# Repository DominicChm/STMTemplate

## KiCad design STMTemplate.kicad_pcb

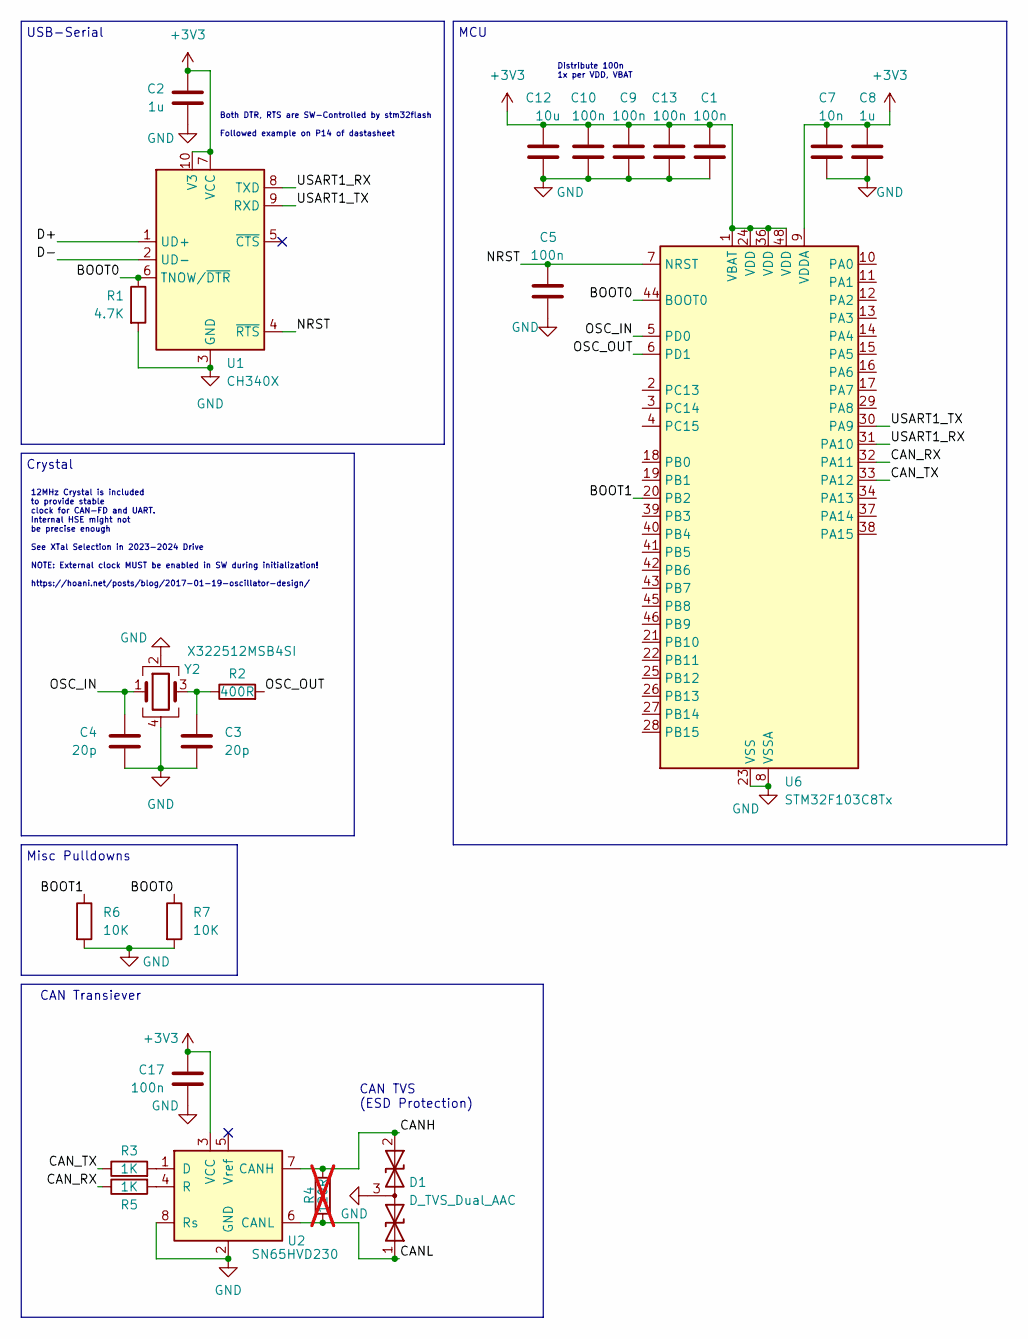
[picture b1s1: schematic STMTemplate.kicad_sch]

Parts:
C1, C5, C9, C10, C13, C17: 100n; C_0402_1005Metric
C2, C8: 1u; C_0402_1005Metric
C3, C4: 20p; C_0402_1005Metric
C7: 10n; C_0402_1005Metric
C12: 10u; C_0402_1005Metric
D1: D_TVS_Dual_AAC; SOT-23-3; LCSC C32677
R1: 4.7K; R_0402_1005Metric
R2: 400R; R_0402_1005Metric
R3, R5: 1K; R_0402_1005Metric
R4: 120R; R_1206_3216Metric; not fitted
R6, R7: 10K; R_0402_1005Metric
U1: CH340X; MSOP-10_3x3mm_P0.5mm
U2: SN65HVD230; SOIC-8_3.9x4.9mm_P1.27mm
U6: STM32F103C8Tx; LQFP-48_7x7mm_P0.5mm
Y2: X322512MSB4SI; Crystal_SMD_3225-4Pin_3.2x2.5mm; LCSC C9002

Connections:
+3V3: C1.1, C2.1, C7.1, C8.1, C9.1, C10.1, C12.1, C13.1, C17.1, U1.7 (VCC), U1.10 (V3), U2.3 (VCC), U6.1 (VBAT), U6.9 (VDDA), U6.24 (VDD), U6.36 (VDD), U6.48 (VDD)
/BOOT0: R1.1, R7.1, U1.6 (TNOW/~DTR), U6.44 (BOOT0)
/BOOT1: R6.1, U6.20 (PB2)
/CANH: D1.2 (A2), R4.1, U2.7 (CANH)
/CANL: D1.1 (A1), R4.2, U2.6 (CANL)
/CAN_RX: R5.1, U6.32 (PA11)
/CAN_TX: R3.1, U6.33 (PA12)
/D+: U1.1 (UD+)
/D-: U1.2 (UD-)
/NRST: C5.1, U1.4 (~RTS), U6.7 (NRST)
/OSC_IN: C4.1, U6.5 (PD0), Y2.1
/OSC_OUT: R2.2, U6.6 (PD1)
/USART1_RX: U1.8 (TXD), U6.31 (PA10)
/USART1_TX: U1.9 (RXD), U6.30 (PA9)
GND: C1.2, C2.2, C3.2, C4.2, C5.2, C7.2, C8.2, C9.2, C10.2, C12.2, C13.2, C17.2, D1.3 (common), R1.2, R6.2, R7.2, U1.3 (GND), U2.2 (GND), U2.8 (Rs), U6.8 (VSSA), U6.23 (VSS), U6.35 (VSS), U6.47 (VSS), Y2.2, Y2.4
unnamed: C3.1, R2.1, Y2.3
unnamed: R3.2, U2.1 (D)
unnamed: R5.2, U2.4 (R)

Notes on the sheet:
USB-Serial
Crystal
Misc Pulldowns
Distribute 100n 1x per VDD, VBAT
https://hoani.net/posts/blog/2017-01-19-oscillator-design/
CAN TVS (ESD Protection)
12MHz Crystal is included to provide stable clock for CAN-FD and UART. Internal HSE might not be precise enough See XTal Selection in 2023-2024 Drive NOTE: External clock MUST be enabled in SW during initialization!
CAN Transiever
Both DTR, RTS are SW-Controlled by stm32flash Followed example on P14 of dastasheet
MCU

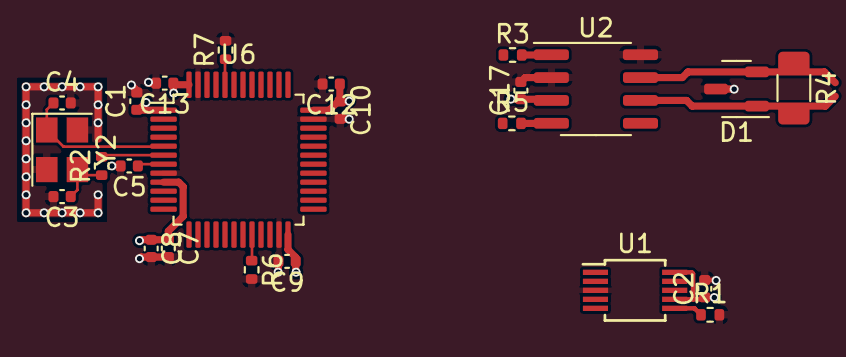
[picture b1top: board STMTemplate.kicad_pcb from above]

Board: 4 copper layers, 24 parts (0 on the bottom side), 16 nets.
